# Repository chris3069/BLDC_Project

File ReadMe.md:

# BLDC source code and electronics

# Electronics
## Schematics:

## Design and Routing

## 3D Electric Design:
### Frontside 

### Backside

# SW

## Open Loop Control

## Closed Loop Control

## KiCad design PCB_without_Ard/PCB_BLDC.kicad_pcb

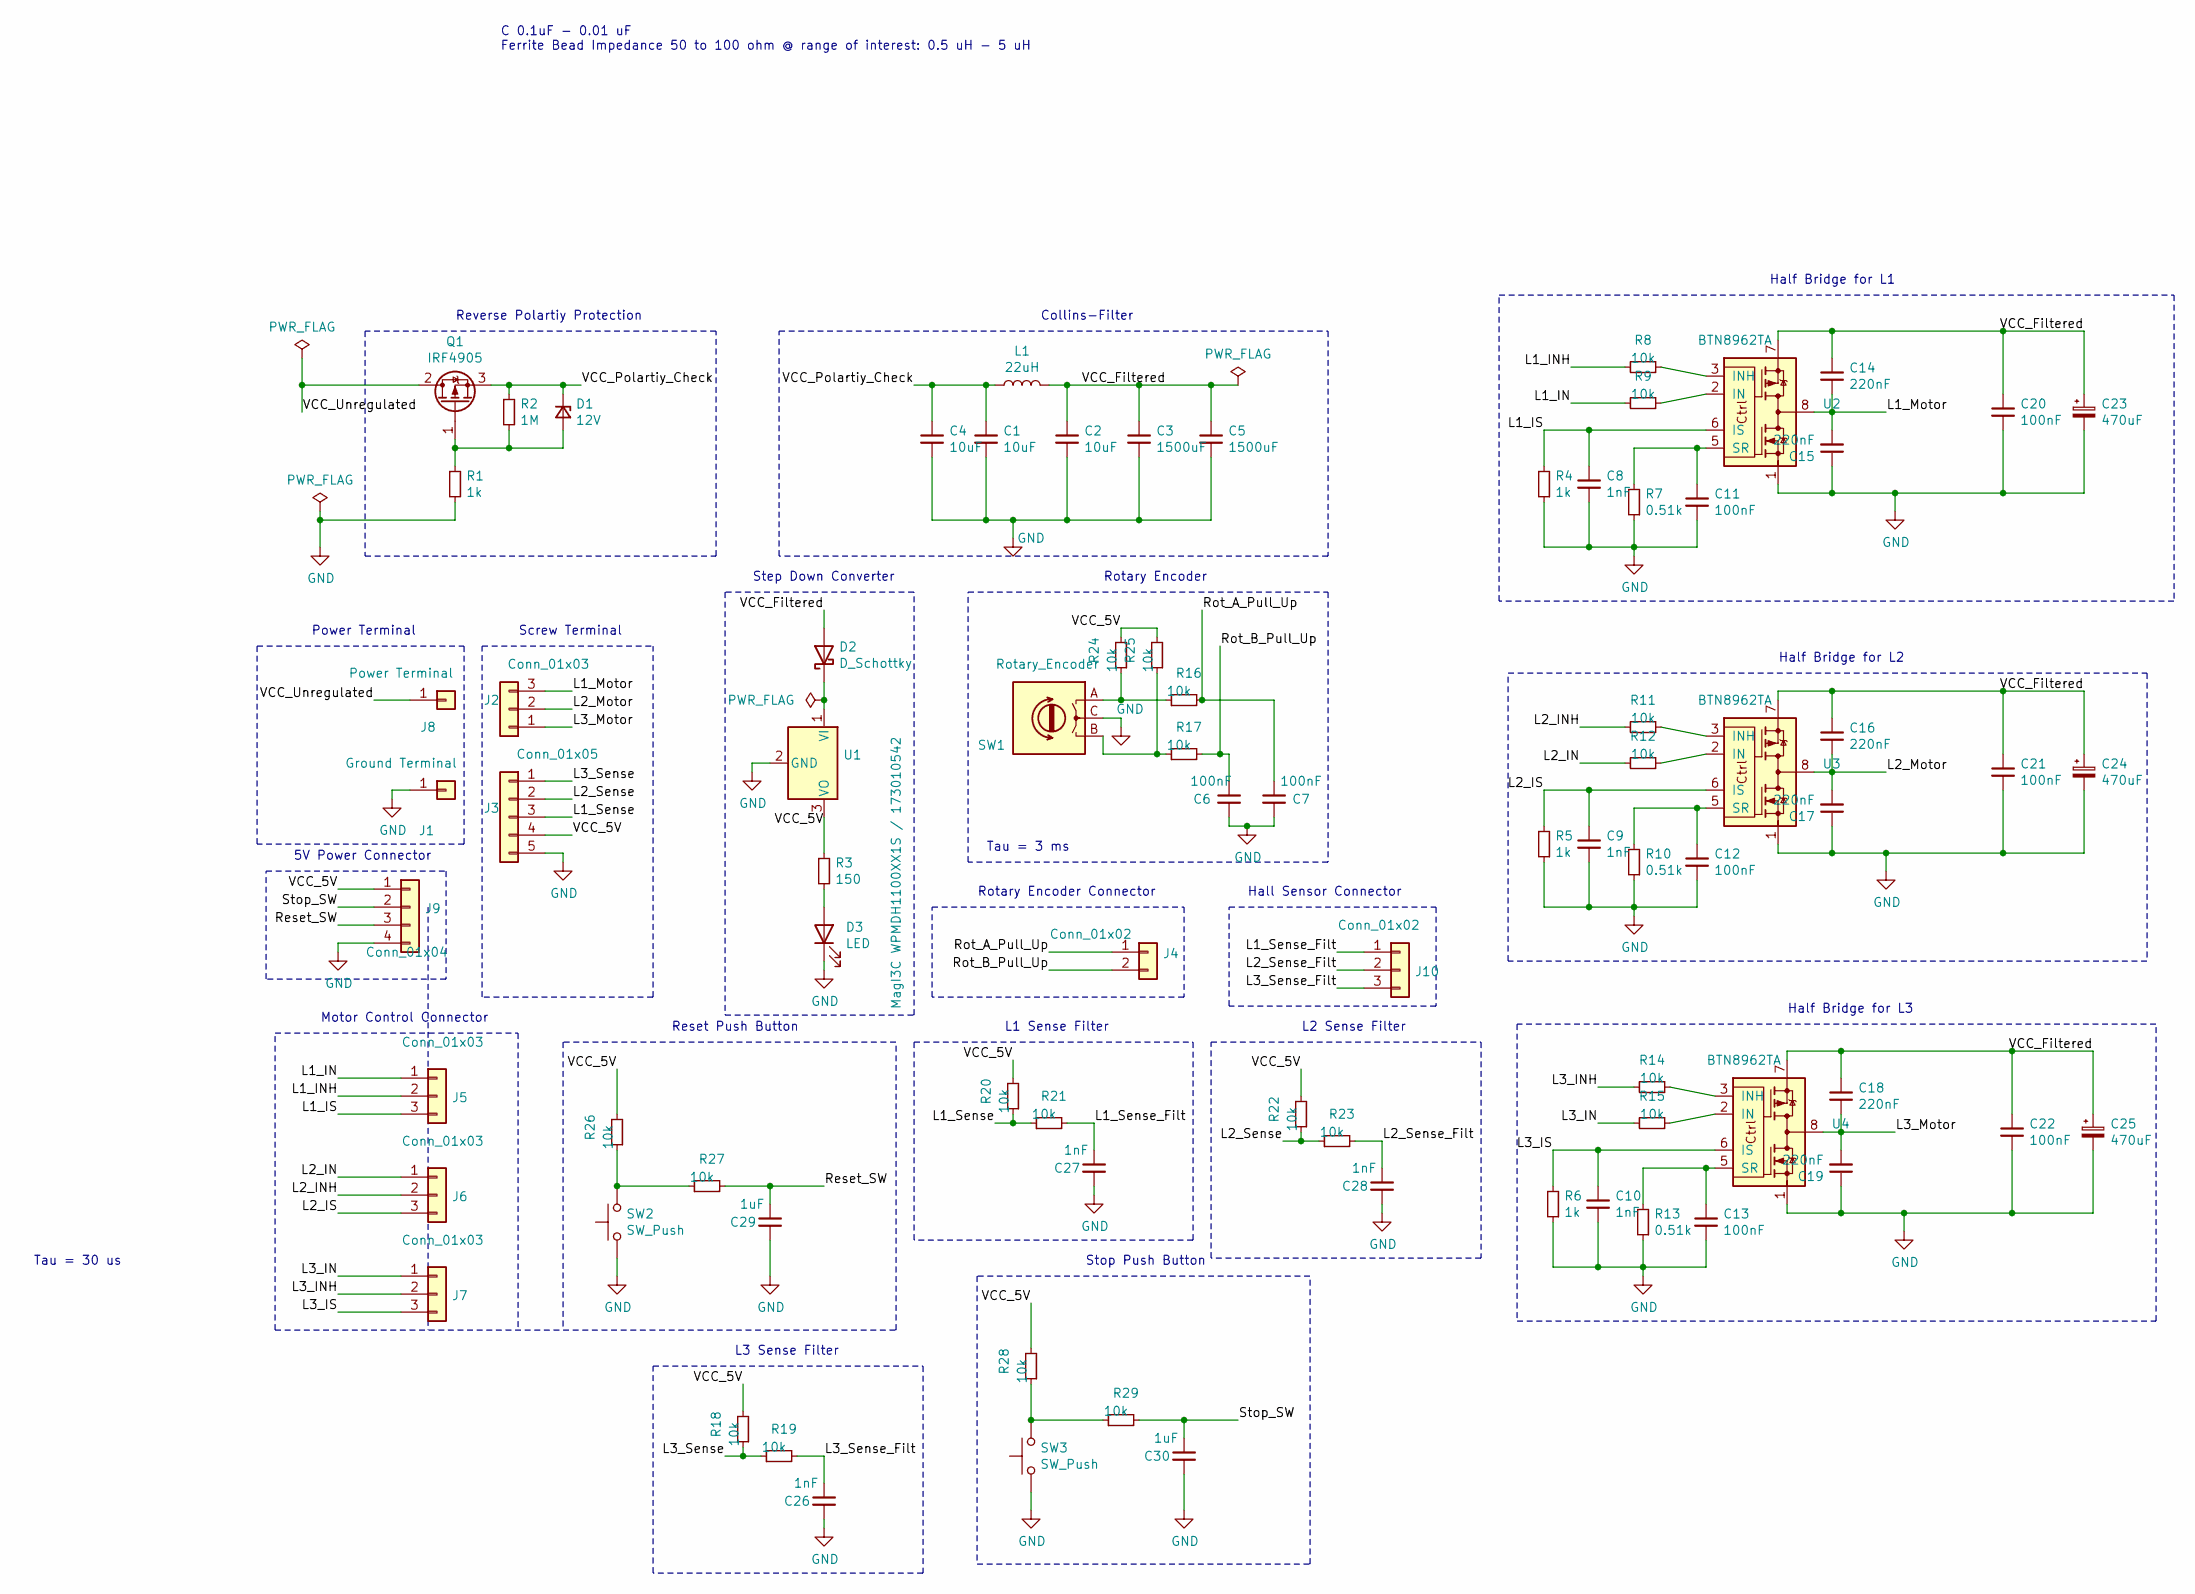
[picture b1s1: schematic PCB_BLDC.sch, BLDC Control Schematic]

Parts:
C1, C2, C4: 10uF; C_1210_3225Metric_Pad1.33x2.70mm_HandSolder
C3, C5: 1500uF; CP_Elec_16x17.5
C6, C7, C11, C12, C13, C20, C21, C22: 100nF; C_1206_3216Metric_Pad1.33x1.80mm_HandSolder
C8, C9, C10, C26, C27, C28: 1nF; C_1206_3216Metric_Pad1.33x1.80mm_HandSolder
C14, C15, C16, C17, C18, C19: 220nF; C_1206_3216Metric_Pad1.33x1.80mm_HandSolder
C23, C24, C25: 470uF; CP_Elec_16x17.5
C29, C30: 1uF; C_1206_3216Metric_Pad1.33x1.80mm_HandSolder
D1: 12V; D_SOD-123
D2: D_Schottky; D_SMB_Handsoldering
D3: LED; LED_1206_3216Metric_Pad1.42x1.75mm_HandSolder
J1: Ground Terminal; CalTest_CT3151
J2: Conn_01x03; TerminalBlock_Phoenix_MKDS-1,5-3_1x03_P5.00mm_Horizontal
J3: Conn_01x05; TerminalBlock_Phoenix_MKDS-1,5-5_1x05_P5.00mm_Horizontal
J4: Conn_01x02; PinSocket_1x02_P2.54mm_Vertical
J5, J6, J7: Conn_01x03; PinSocket_1x03_P2.54mm_Vertical
J8: Power Terminal; CalTest_CT3151
J9: Conn_01x04; PinSocket_1x04_P2.54mm_Vertical
J10: Conn_01x02; PinSocket_1x03_P2.54mm_Vertical
L1: 22uH; L_Wuerth_WE-PD-Typ-LS_Handsoldering
Q1: IRF4905; TO-263-2
R1, R4, R5, R6: 1k; R_1206_3216Metric_Pad1.30x1.75mm_HandSolder
R2: 1M; R_1206_3216Metric_Pad1.30x1.75mm_HandSolder
R3: 150; R_1206_3216Metric_Pad1.30x1.75mm_HandSolder
R7, R10, R13: 0.51k; R_1206_3216Metric_Pad1.30x1.75mm_HandSolder
R8, R9, R11, R12, R14, R15, R16, R17, R18, R19, R20, R21, R22, R23, R24, R25, R26, R27, R28, R29: 10k; R_1206_3216Metric_Pad1.30x1.75mm_HandSolder
SW1: Rotary_Encoder; RotaryEncoder_Alps_EC12E-Switch_Vertical_H20mm
SW2, SW3: SW_Push; SW_PUSH-12mm_Wuerth-430476085716
U1: MagI3C WPMDH1100XX1S / 173010542; SIP3_11.6x8.5mm
U2, U3, U4: BTN8962TA; TO-263-7_TabPin8

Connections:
/L1_IN: J5.1, R9.2
/L1_INH: J5.2, R8.2
/L1_IS: C8.1, J5.3, R4.2, U2.6 (IS)
/L1_Motor: C14.2, C15.2, J2.3, U2.4, U2.8
/L1_Sense: J3.3, R20.1, R21.1
/L1_Sense_Filt: C27.1, J10.1, R21.2
/L2_IN: J6.1, R12.2
/L2_INH: J6.2, R11.2
/L2_IS: C9.1, J6.3, R5.2, U3.6 (IS)
/L2_Motor: C16.2, C17.2, J2.2, U3.4, U3.8
/L2_Sense: J3.2, R22.1, R23.1
/L2_Sense_Filt: C28.1, J10.2, R23.2
/L3_IN: J7.1, R15.2
/L3_INH: J7.2, R14.2
/L3_IS: C10.1, J7.3, R6.2, U4.6 (IS)
/L3_Motor: C18.2, C19.2, J2.1, U4.4, U4.8
/L3_Sense: J3.1, R18.1, R19.1
/L3_Sense_Filt: C26.1, J10.3, R19.2
/Reset_SW: C29.1, J9.3, R27.2
/Rot_A_Pull_Up: C7.1, J4.1, R16.2
/Rot_B_Pull_Up: C6.1, J4.2, R17.2
/Stop_SW: C30.1, J9.2, R29.2
/VCC_5V: J3.4, J9.1, R3.1, R18.2, R20.2, R22.2, R24.2, R25.2, R26.2, R28.2, U1.3 (VO)
/VCC_Filtered: C2.1, C3.1, C5.1, C14.1, C16.1, C18.1, C20.1, C21.1, C22.1, C23.1, C24.1, C25.1, D2.2 (A), L1.2, U2.7, U3.7, U4.7
/VCC_Polartiy_Check: C1.1, C4.1, D1.1 (K), L1.1, Q1.3 (S), R2.1
/VCC_Unregulated: J8.1, Q1.2 (D)
GND: C1.2, C2.2, C3.2, C4.2, C5.2, C6.2, C7.2, C8.2, C9.2, C10.2, C11.2, C12.2, C13.2, C15.1, C17.1, C19.1, C20.2, C21.2, C22.2, C23.2, C24.2, C25.2, C26.2, C27.2, C28.2, C29.2, C30.2, D3.1 (K), J1.1, J3.5, J9.4, R1.2, R4.1, R5.1, R6.1, R7.1, R10.1, R13.1, SW1.C, SW2.1, SW3.1, U1.2 (GND), U2.1, U3.1, U4.1
unnamed: C11.1, R7.2, U2.5 (SR)
unnamed: C12.1, R10.2, U3.5 (SR)
unnamed: C13.1, R13.2, U4.5 (SR)
unnamed: D1.2 (A), Q1.1 (G), R1.1, R2.2
unnamed: D2.1 (K), U1.1 (VI)
unnamed: D3.2 (A), R3.2
unnamed: R8.1, U2.3 (INH)
unnamed: R9.1, U2.2 (IN)
unnamed: R11.1, U3.3 (INH)
unnamed: R12.1, U3.2 (IN)
unnamed: R14.1, U4.3 (INH)
unnamed: R15.1, U4.2 (IN)
unnamed: R16.1, R24.1, SW1.A
unnamed: R17.1, R25.1, SW1.B
unnamed: R26.1, R27.1, SW2.2
unnamed: R28.1, R29.1, SW3.2

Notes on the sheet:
C 0.1uF - 0.01 uF Ferrite Bead Impedance 50 to 100 ohm @ range of interest: 0.5 uH - 5 uH
Collins-Filter
Reverse Polartiy Protection
Half Bridge for L1
Screw Terminal
Rotary Encoder
Step Down Converter
Half Bridge for L2
Half Bridge for L3
Tau = 30 us
Tau = 3 ms
Power Terminal
5V Power Connector
Rotary Encoder Connector
Motor Control Connector
Reset Push Button
Hall Sensor Connector
L2 Sense Filter
L3 Sense Filter
L1 Sense Filter
Stop Push Button

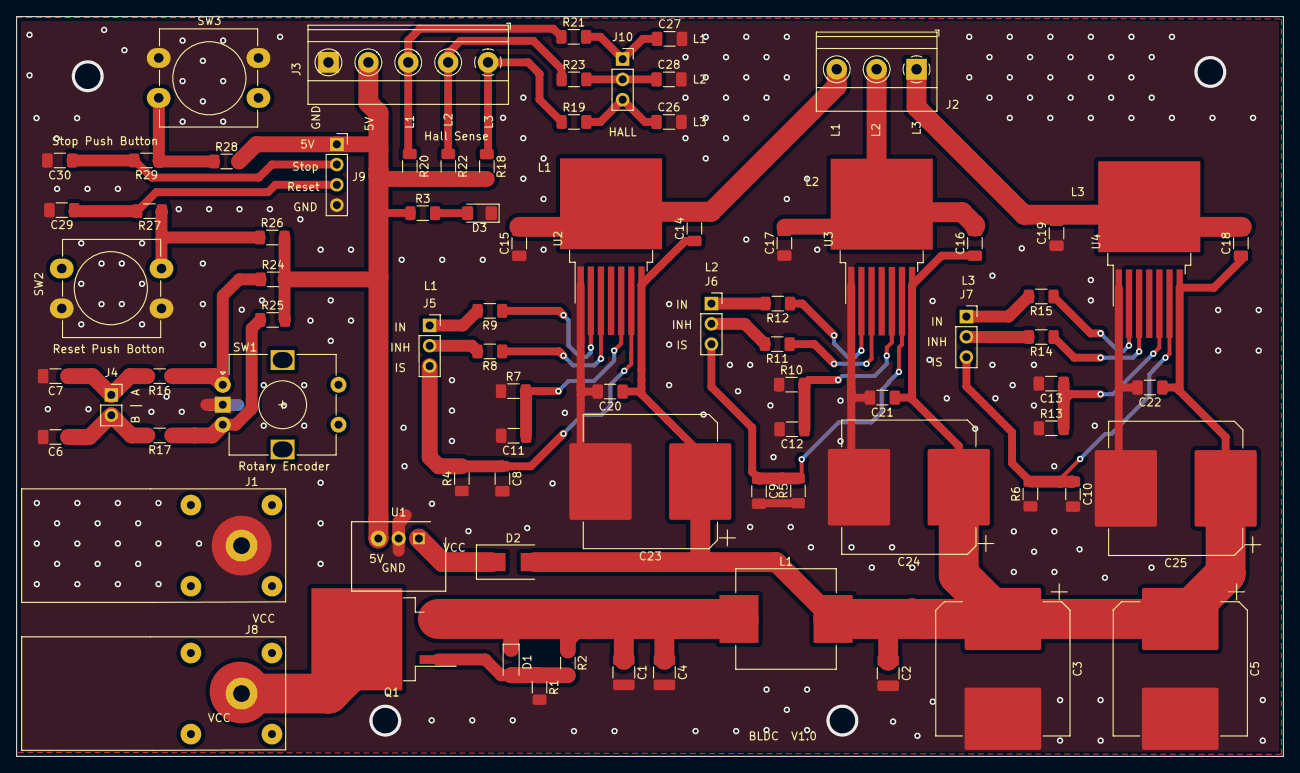
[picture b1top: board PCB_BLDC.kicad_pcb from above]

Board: 2 copper layers, 158.8 x 92.7 mm, 81 parts (0 on the bottom side), 43 nets.

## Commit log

2021-10-21 Main: Inital Commit for BLDC Project
2021-10-21 Main: Start Schmeatic Layout
2021-10-22 Main: Update Schematic Start PCB-Layout
2021-10-29 Main: Improve Schematic
2021-10-29 Main: Update Schematic
2021-10-30 Main: Update Schmeatics and PCB
2021-10-31 Main: Trace Routing @ PCB
2021-11-01 Main: Update Footprint, PCB Layout
2021-11-01 Main: Update Schmeatics, Add VCC
2021-11-04 Main: Update Arduino Pins, PCB Routing
2021-11-05 Main: Update Routing, Schmematic to use Analog Ports of Arduino
2021-11-06 Main: Finish PCB Routing Add Filled Zone Texts
2021-11-06 Main: Add Text to Schematic and PCB, Images
2021-11-06 PCB: Add Images, PDFs, Gerber-Files
2021-11-06 Main: Update PCB, Add Vias, Update Schematic, Update Netlist
2021-11-08 PCB: New PCB without Arduino and smaaler size made
2021-11-08 Main: Update Schematic, Add Vias, RC-Filt for Hall-Sense
2021-11-09 PCB: Fixed again Low Pass Filter
2021-11-12 PCB: Changed Power Terminals to correct one, Adapted csv-File to PT1-Filter
2021-11-13 Minor adjustments @ THT size csv and resistor values
2021-11-14 Remove RC-Filter for Hall Sensors
2021-11-14 Add Push Button to Reset the System
2021-11-14 PCB: Change Position of RC Filt for Hall Sense and Position of Connector
2021-11-15 PCB: Add *.pdf and update gerber files
2021-11-15 PCB: Final Review. Add new Push Button, Change wrong Capacitors Change Routing, Add Mounting Holes
2021-11-15 PCB: Add Image Output to view it easier
2021-11-26 PCB: Fix Folder structure - Delete old design with arduino - Clean SW folder strucutre
2021-11-26 SW: Make Working Digital Poti - Call Motor functions - TODO: Include .c files to platform.ini to sovle linking error
2021-11-26 SW: Basic Open Loop setup for BLDC Motor Control
2021-11-27 SW: Add push button functionality
    - rework architecture
2021-11-27 Open Loop Motor Control is working
2021-11-28 SW_new_Architect: Update to OOP
    - L3 is behaving weiredly. Is counter acting 1 duty cicly, and 1 is ok
    - Current consume has doubled to 4-5 Amps
2021-11-28 SW_new_Architect: Fix bug which caused too long period for L3
    - Bug was probably caused by weired initialization:
    - Motor_Implementation was globally defined
    - was kind off preinitialized probably because it was on stack
    - start speed control with Hall sense
2021-12-02 SW_new_Architecture: Add Control loop with PI Controller and current sense
    - Current Sense has to be finetuned with R_shunt and gain value
2021-12-02 SW_new_Architect: Fix correct init of Closed Loop
    - Motor behaves really weiredly, almost like angle control with extrem fast
    direction in change randomly, demands sometime very much current, without moving
2021-12-03 Closed Loop Control working with example script,
    - Paramter number polepairs and number hallsense wrongly set
2021-12-03 SW_new_Architect:Removed Logging for better performance
2021-12-04 SW_new_Architect: Add Current Sense with arbitrary values
    - Motor works as it is supposed to
2021-12-22 PCB: Add Documentation images to PCB Layout
2022-01-20 pyhton script for genertating sine wave start for hw Layer on stm32f446re
2022-01-22 STM SW with Class Strcuture for Motor
2022-01-22 Functioning Open Loop Control with Start and Stop functionality
2022-01-29 Finish Open Loop functionality
2022-01-30 Add Readme
    - gnerate Hall Files
2022-02-02 Update Hall module
2022-02-03 refactor code, abstarct motor_phase, generate sinusodal and bock_com refacotr motor_implementation
2022-02-03 refactor motor_implementation
2022-02-04 Closed Loop with Block Commutation working
2022-02-06 Closed Loop functions
2022-02-07 Add possibily to start as open_loop or closed loop depending on start_pin_level
